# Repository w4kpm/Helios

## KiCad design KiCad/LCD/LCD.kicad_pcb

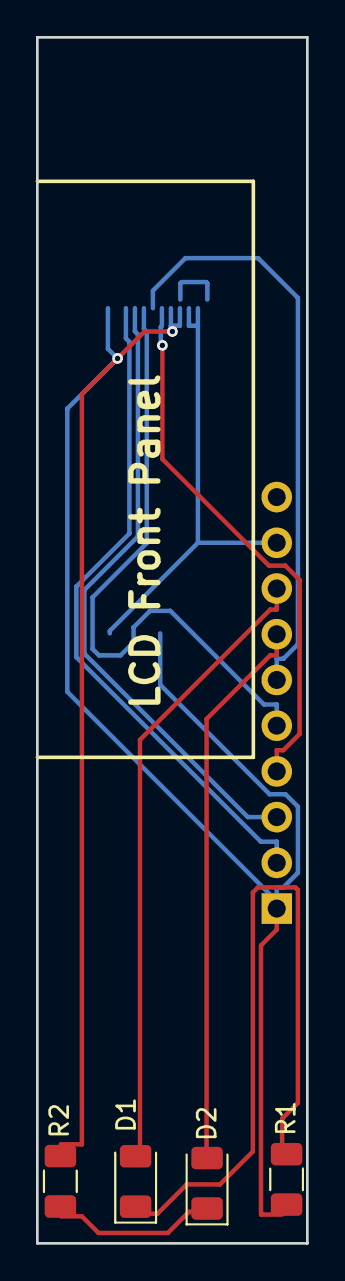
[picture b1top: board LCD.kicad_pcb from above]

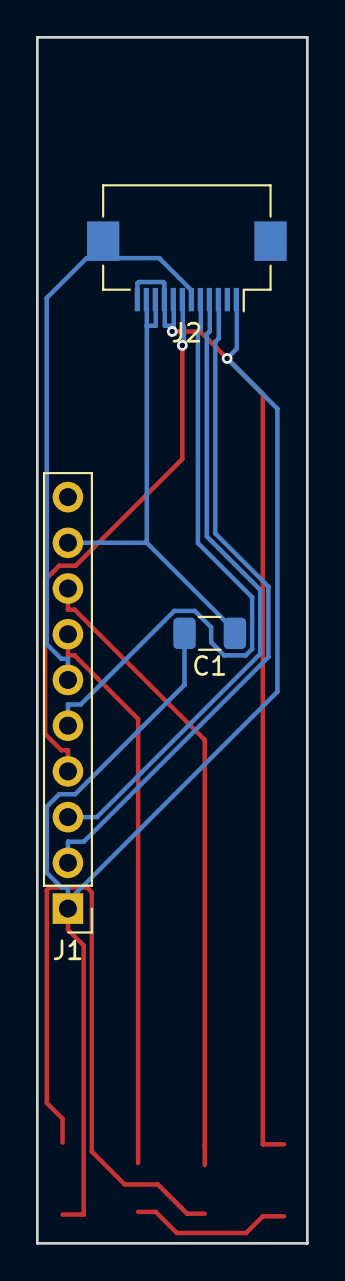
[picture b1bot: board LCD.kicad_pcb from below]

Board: 2 copper layers, 15.0 x 67.0 mm, 7 parts (3 on the bottom side), 11 nets.

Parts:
C1: 1uf; C_1206_3216Metric
D1, D2: LED; LED_1206_3216Metric
J1: Conn_01x10; Pin_Header_Straight_1x10_Pitch2.54mm
J2: Conn_01x12; Hirose_FH12-12S-0.5SH_1x12-1MP_P0.50mm_Horizontal
R1, R2: 300; R_1206_3216Metric

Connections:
+3V3: C1.1, J1.9, J2.10, J2.11
GND: C1.2, J1.1, J2.1, J2.8, J2.9, J2.12, R1.1, R2.1
unnamed: D1.1, R1.2
unnamed: D1.2, J1.8
unnamed: D2.1, R2.2
unnamed: D2.2, J1.7
unnamed: J1.2, J2.3
unnamed: J1.3, J2.4
unnamed: J1.4, J2.7
unnamed: J1.5, J2.5
unnamed: J1.6, J2.6

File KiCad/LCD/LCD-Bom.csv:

"Item","Qty","Reference(s)","Value","LibPart","Footprint","Datasheet"
"1","1","C1","1uf","Device:C","Capacitor_SMD:C_1206_3216Metric","~"
"2","2","D1, D2","LED","Device:LED","LED_SMD:LED_1206_3216Metric","~"
"3","1","J1","Conn_01x10","Connector_Generic:Conn_01x10","Connector_PinHeader_2.54mm:PinHeader_1x10_P2.54mm_Vertical","~"
"4","1","J2","Conn_01x12","Connector_Generic:Conn_01x12","Amphenol SFV12R-4STBE1HLF P0.50mm_Horizontal","~"
"5","2","R1, R2","300","Device:R","Resistor_SMD:R_1206_3216Metric","~"

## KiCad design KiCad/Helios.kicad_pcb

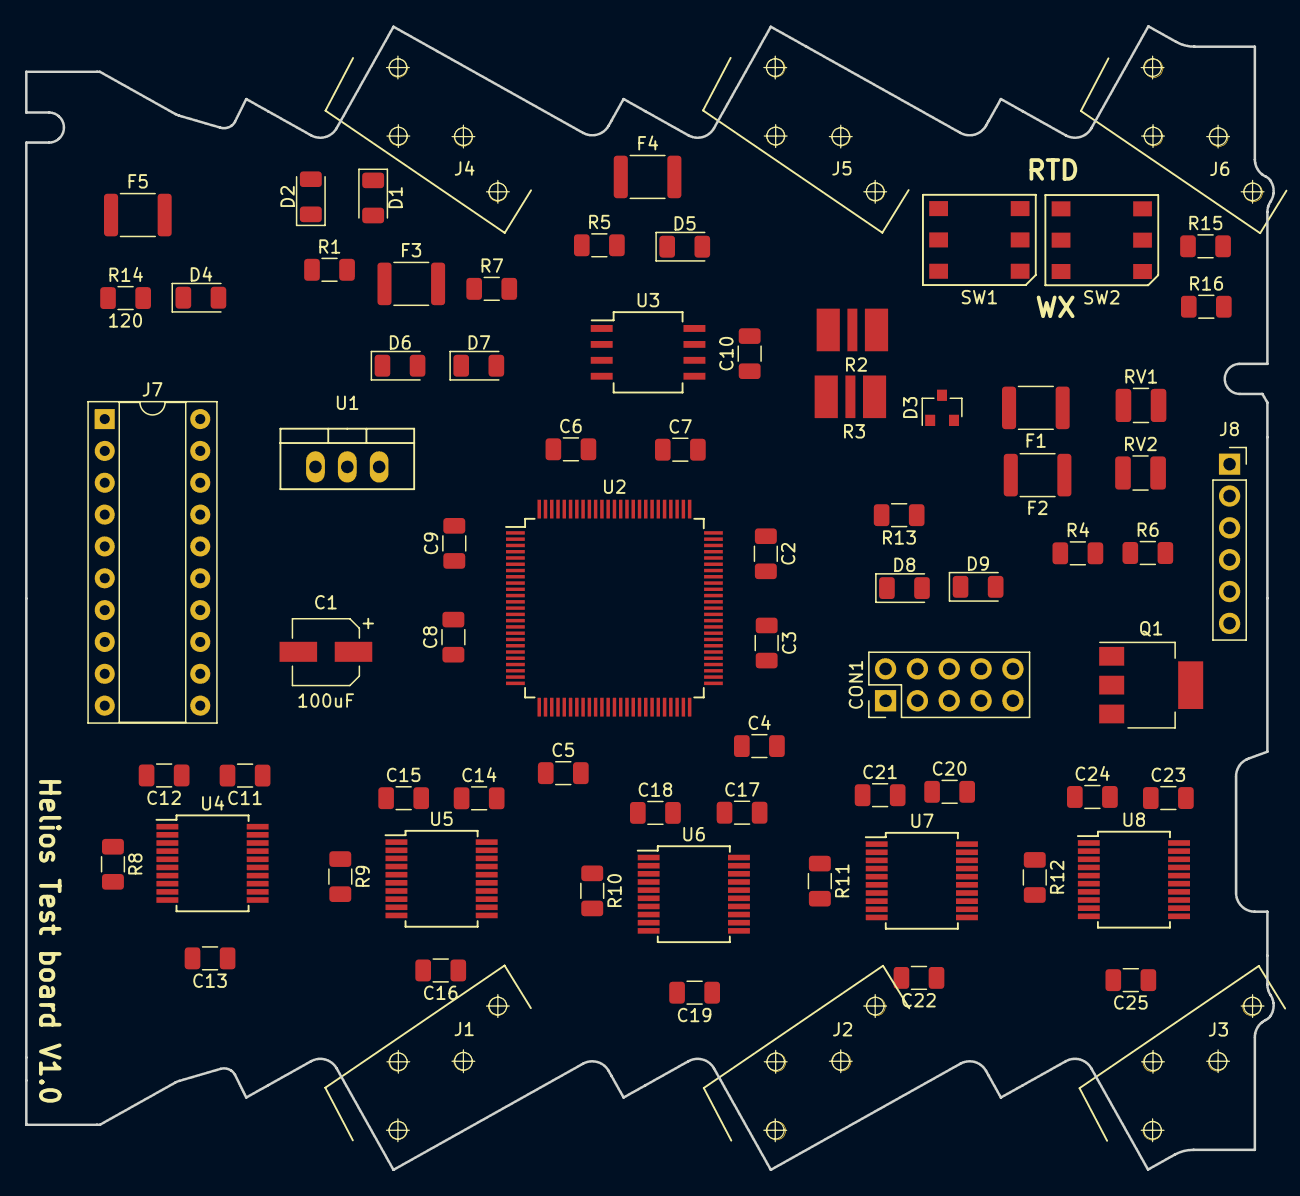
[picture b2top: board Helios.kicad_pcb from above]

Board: 2 copper layers, 99.5 x 91.2 mm, 77 parts (0 on the bottom side), 80 nets, no tracks yet.

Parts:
C1: 100uF; CP_Elec_5x5.3
C2, C4, C6, C8: 1 uF; C_1206_3216Metric
C3, C5, C7, C9, C10, C11, C12, C13, C14, C15, C16, C17, C18, C19, C20, C21, C22, C23, C24, C25: .1 uF; C_1206_3216Metric
CON1: AVR-JTAG-10; Pin_Header_Straight_2x05_Pitch2.54mm
D1, D2, D4, D5, D6, D7, D8, D9: D_Schottky; D_1206_3216Metric
D3: D_TVS_x2_AAC; SOT-23
F1, F2, F3, F4, F5: Polyfuse_Small; R_1812_4532Metric
J1, J2, J3: Conn_01x04; CH20Mr
J4, J5, J6: Conn_01x04; CH20Mt
J7: Conn_02x10_Counter_Clockwise; DIP-20_W7.62mm_Socket
J8: Conn_01x06; PinSocket_1x06_P2.54mm_Vertical
Q1: Q_NMOS_GDS; SOT-223-3_TabPin2
R1: 0; R_1206_3216Metric
R2, R3: TBU
R4: 9k; R_1206_3216Metric
R5, R14: 120; R_1206_3216Metric
R6: 1k; R_1206_3216Metric
R7, R13, R15, R16: 10k; R_1206_3216Metric
R8, R9, R10, R11, R12: 430 .1%; R_1206_3216Metric
RV1, RV2: Varistor; R_1210_3225Metric
SW1, SW2: SW_DPDT_x2; DPDT
U1: LM78l33_TO220; TO-220_Neutral123_Vertical
U2: STM32F303V(B-C)Tx_u; LQFP-100_14x14mm_Pitch0.5mm
U3: SN65HV7X; SO-8_5.3x6.2mm_Pitch1.27mm
U4, U5, U6, U7, U8: MAX31865; SSOP-20_5.3x7.2mm_Pitch0.65mm

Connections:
+3V3: C1.1, C2.1, C3.1, C4.1, C5.1, C6.1, C7.1, C8.1, C9.1, C10.2, C11.2, C12.2, C14.2, C15.2, C17.2, C18.2, C20.2, C21.2, C23.2, C24.2, CON1.4, D6.1, D8.1, J7.9, J7.12, R16.1, U1.3, U2.6, U2.21, U2.22, U2.28, U2.50, U2.75, U2.100, U3.8, U4.2, U4.3, U5.2, U5.3, U6.2, U6.3, U7.2, U7.3, U8.2, U8.3
+24V: D2.1, J7.10, J7.11, R13.2, U1.1
/GPIOA/serial/RX: U2.26, U3.1
/GPIOA/serial/TX: U2.25, U3.4
/GPIOA/serial/TX_en: U2.24, U3.2, U3.3
/GPIOB/485RX: J7.8, J7.13, U2.97
/GPIOB/485TX: J7.7, J7.14, U2.98
/GPIOB/D/~C: J7.5, J7.16, U2.53
/GPIOB/MOSI: J7.2, J7.19, U2.54
/GPIOB/SCK: J7.3, J7.18, U2.52
/GPIOB/UART1_RX: J8.4, U2.93
/GPIOB/UART1_TX: J8.5, U2.92
/GPIOB/~CS: J7.4, J7.17, U2.48
/GPIOF/~reset: J7.6, J7.15, U2.11
/Pyro: F3.2, J4.4
/RS485A: F2.1, J5.1, RV2.1
/RS485B: F1.1, J5.2, RV1.1
/Snow: J6.4, Q1.2, R4.2, R13.1
/Wind: F4.2, J5.4
Aux: SW2.5, U2.64
GND: C1.2, C2.2, C3.2, C4.2, C5.2, C6.2, C7.2, C8.2, C9.2, C10.1, C11.1, C12.1, C14.1, C15.1, C17.1, C18.1, C20.1, C21.1, C23.1, C24.1, CON1.2, D3.3, D4.2, D5.2, D7.2, D9.2, J4.3, J5.3, J7.1, J7.20, J8.1, Q1.3, R1.1, R5.2, R6.2, R7.2, R14.2, R15.1, RV1.2, RV2.2, SW1.4, U1.2, U2.20, U2.49, U2.74, U2.94, U2.99, U3.5, U4.13, U4.18, U4.19, U5.13, U5.18, U5.19, U6.13, U6.18, U6.19, U7.13, U7.18, U7.19, U8.13, U8.18, U8.19
GNDPWR: D1.1, J4.2
unnamed: CON1.1, U2.76
unnamed: CON1.5, U2.72
unnamed: D1.2, R1.2
unnamed: D2.2, J4.1
unnamed: D3.1, F2.2, R3.1
unnamed: D3.2, F1.2, R2.1
unnamed: D4.1, F5.1, R14.1, U2.61
unnamed: D5.1, F4.1, R5.1, U2.60
unnamed: D6.2, D7.1, F3.1, R7.1, U2.58, U2.59
unnamed: D8.2, D9.1, R4.1, R6.1, U2.56
unnamed: J6.1, SW1.2
unnamed: J6.2, SW1.5
unnamed: J6.3, SW2.2
unnamed: Q1.1, U2.57
unnamed: R2.2, U3.7
unnamed: R3.2, U3.6
unnamed: R8.1, U4.4, U4.5
unnamed: R8.2, U4.6, U4.7
unnamed: R9.1, U5.4, U5.5
unnamed: R9.2, U5.6, U5.7
unnamed: R10.1, U6.4, U6.5
unnamed: R10.2, U6.6, U6.7
unnamed: R11.1, U7.4, U7.5
unnamed: R11.2, U7.6, U7.7
unnamed: R12.1, U8.4, U8.5
unnamed: R12.2, U8.6, U8.7
unnamed: R15.2, SW2.4
unnamed: R16.2, SW2.6
RTD-1: C13.1, J3.1, U4.11, U4.12
RTD-2: C16.1, J3.2, U5.11, U5.12
RTD-3: C19.1, J3.3, U6.11, U6.12
RTD-4: C22.1, J3.4, U7.11, U7.12
RTD-5: C25.1, SW2.3, U8.11, U8.12
RTD_MISO: U2.79, U4.17, U5.17, U6.17, U7.17, U8.17
RTD_MOSI: U2.80, U4.14, U5.14, U6.14, U7.14, U8.14
RTD_SCK: U2.78, U4.15, U5.15, U6.15, U7.15, U8.15
RTDa1: J1.1, U4.8, U4.9
RTDa2: J1.2, U5.8, U5.9
RTDa3: J1.3, U6.8, U6.9
RTDa4: J1.4, U7.8, U7.9
RTDa5: SW1.3, U8.8, U8.9
RTDb1: C13.2, J2.1, U4.10
RTDb2: C16.2, J2.2, U5.10
RTDb3: C19.2, J2.3, U6.10
RTDb4: C22.2, J2.4, U7.10
RTDb5: C25.2, SW1.6, U8.10
Rain: SW1.1, U2.63
WindDir: F5.2, SW2.1
~DRDY1: U2.81, U4.1
~DRDY2: U2.82, U5.1
~DRDY3: U2.83, U6.1
~DRDY4: U2.84, U7.1
~DRDY5: U2.85, U8.1
~RTDcs1: U2.15, U4.16
~RTDcs2: U2.16, U5.16
~RTDcs3: U2.17, U6.16
~RTDcs4: U2.18, U7.16
~RTDcs5: U2.33, U8.16

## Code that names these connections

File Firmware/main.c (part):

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  palSetPadMode(GPIOD, 12, PAL_MODE_INPUT_ANALOG);
  
  palSetPadMode(GPIOD, 13, PAL_MODE_INPUT_ANALOG);
  palSetPadMode(GPIOD, 14, PAL_MODE_INPUT_ANALOG); // wind dir


  
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  palSetPadMode(GPIOC, 4, PAL_MODE_OUTPUT_PUSHPULL); // rtd 4
  //palSetPadMode(GPIOC, 5, PAL_MODE_OUTPUT_PUSHPULL); // common line
  palSetPadMode(GPIOC, 6, PAL_MODE_INPUT_PULLUP); // raingauge
  palSetPadMode(GPIOC, 7, PAL_MODE_INPUT_PULLUP); // rain enabled
  palSetPad(GPIOC,0);
  palClearPad(GPIOD,10);
  palSetPad(GPIOC,1);
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	  windspeed = (amps-0.004)*(50.0/.016);
	  winddir = windamps*360.0/.02;
	  if (winddir <0)
	    winddir = 0;
	  if (winddir > 360.0)
	    winddir = 360;
	  opamp4 = calc_volts(VDD,samples2[3]);
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
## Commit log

2018-05-08 Initial add
2018-05-08 remove build files
2018-05-09 Got everything running back as it was before I started updating ChibiOS
2018-05-09 Added ADC for Temp sensor on chip, and got floating point numbers printing out
2018-06-01 added wind sensor
2018-06-11 Added use of opamp to boost irradiance and get a more accurate reading
2018-06-11 added KiCad directory
2018-06-12 added spi interface to pt100
2018-06-21 update schematics
2018-06-21 added both LCD and Temp sensor
2018-06-21 yup, we really want myparts.lib
2018-06-22 checkpoint - added RTD blocks but they still need to be finished
2018-06-23 ran drc check and fixed all parts
2018-06-23 added board outline
2018-06-25 finish schematic and start board layout
2018-06-25 added CH20m part footprint
2018-06-26 start board routing
2018-07-03 moved a few adc things aronud
2018-07-26 save a few changes to the schematic
2018-07-26 make changes to reflect change to new board
2018-07-27 changed how TX and RX Lights work in the code - need to add changes into schematic
2018-07-30 add lcd cutout dxf to repo
2018-07-31 Make changes for new board including multiple temp sensors
2018-07-31 changes to the board layout
2018-07-31 make changes to rx/tx lights
2018-07-31 get rid of intermediat files
2018-08-01 transfer back to other computer
2018-08-01 remove large breakout area for more room on board
2018-08-01 change DXF for board outline
2018-08-01 change outline to new pattern
2018-08-01 getting ready to submit board
2018-08-01 compiled board zip file for export
2018-08-01 rename file because it doesnt upload with zip in the name
2018-08-01 make change to zip name
2018-08-08 added Display rotation and corrected irradiance
2018-08-08 added python testing directory
2018-08-18 only have spi active during read due to Interrupt conflict
2018-08-18 use global text rather than local
2018-08-18 Add more changes in see if it causes any problem
2018-08-18 another step
2018-08-18 Add in code to be able to reset device after we update parameters
2018-08-18 removed comment
2018-08-18 change modbus id
2018-08-20 added ability to set parameters by modbus, fix bug with flash updating
2018-08-31 save and come back to this after we reset
2018-08-31 add baudrate
2018-09-07 added raingauge features;
2018-09-07 updated to reflect most recent version of pymodbus
2018-09-21 Updated firmware and testing for rain collection
2018-12-12 Had problems with it resetting - it turned out to be that it needed O3 instead of O2
2019-02-05 changed setpoint between snow/no snow
2019-02-05 changed board outline
2019-02-05 make a new template for cutting the front panels
2019-06-21 make sure everything is up to date before transfer to CodeCommit
2019-07-25 add changes included for new display
2019-08-14 save all files for LCD
2019-08-30 added everything for latest version of the LCD screen
2019-09-03 had a few things that didnt get checked in to master
2019-09-05 Updated bom
2019-09-10 submittal of circuit board for assembly
2019-09-13 add changes from send to pcbway
2019-09-13 current progress
2020-08-04 final commit
2021-03-17 move changes back in to device

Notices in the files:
Firmware/main.c:
ChibiOS - Copyright (C) 2006..2015 Giovanni Di Sirio
Licensed under the Apache License, Version 2.0 (the "License");
